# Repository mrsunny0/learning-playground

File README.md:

# Learning Playground

## Rules of Documentation

```
# [Header of README.md]
- Convention: <ROOT FOLDER NAME> - <SUBFOLDER NAME>
- Example:

## High level topic
- Example:

### Subsection of major topic
- Example:

##### Emphasized subheader
-Example:
```

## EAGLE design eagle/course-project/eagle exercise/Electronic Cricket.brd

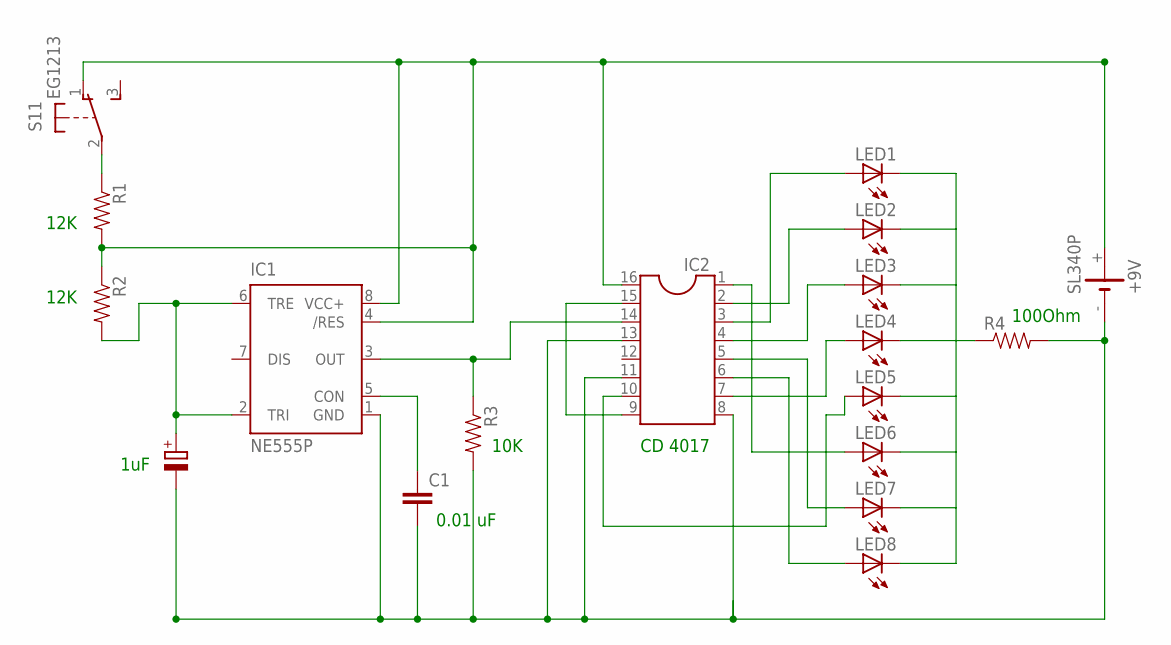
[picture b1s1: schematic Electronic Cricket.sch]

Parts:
+9V: SL340P; SL-340/P3.6V
C1: C2.5/6; C2.5-6
IC1: NE555P; DIL-08
IC2: DIL16
LED1, LED2, LED3, LED4, LED5, LED6, LED7, LED8: LEDB156; Q62902-B156
R1, R2, R3, R4: RESISTORAXIAL-0.3; AXIAL-0.3
S1: EG1213

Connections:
unnamed: IC2.3, LED1.A
unnamed: IC2.2, LED2.A
unnamed: IC2.4, LED3.A
unnamed: IC2.7, LED4.A
unnamed: IC2.10, LED5.A
unnamed: IC2.1, LED6.A
unnamed: IC2.5, LED7.A
unnamed: IC2.9, IC2.15
unnamed: +9V.-, C1.2, IC1.1 (GND), IC2.8, IC2.11, IC2.13, R3.P$2 (2), R4.P$2 (2)
unnamed: IC2.6, LED8.A
unnamed: R1.P$1 (1), S1.2
unnamed: LED1.K (C), LED2.K (C), LED3.K (C), LED4.K (C), LED5.K (C), LED6.K (C), LED7.K (C), LED8.K (C), R4.P$1 (1)
unnamed: IC1.3 (OUT), IC2.14, R3.P$1 (1)
unnamed: +9V.+, IC1.4 (/RES), IC1.8 (VCC+), IC2.16, R1.P$2 (2), R2.P$1 (1), S1.1 (O)
unnamed: IC1.2 (TRI), IC1.6 (TRE), R2.P$2 (2)
unnamed: C1.1, IC1.5 (CON)

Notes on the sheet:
12K
10K
100Ohm
1uF
0.01 uF
CD 4017

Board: 2 copper layers, 17 parts (0 on the bottom side), 16 nets, no tracks yet.

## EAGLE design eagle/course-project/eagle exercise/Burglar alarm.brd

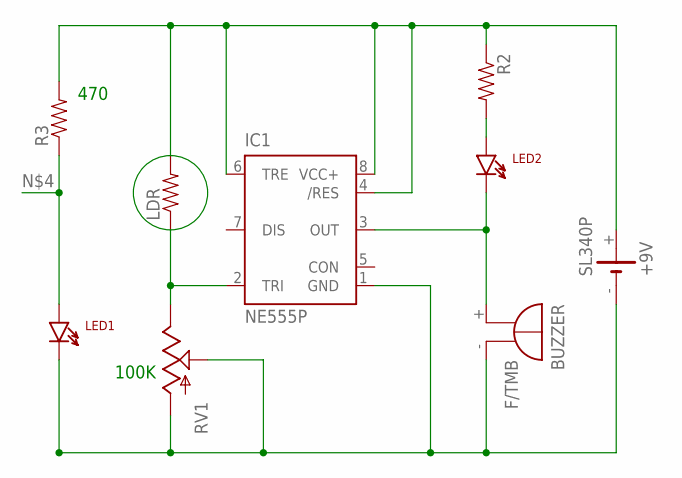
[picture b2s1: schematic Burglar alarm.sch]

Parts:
+9V: SL340P; SL-340/P3.6V
BUZZER: F/TMB
IC1: NE555P; DIL-08
LDR: RESISTORAXIAL-0.3; AXIAL-0.3
LED1, LED2: LTE-302
R2, R3: RESISTORAXIAL-0.3; AXIAL-0.3
RV1: POTTRIM; TRIM_POT

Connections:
unnamed: IC1.2 (TRI), LDR.P$1 (1), RV1.2 (E)
unnamed: BUZZER.+, IC1.3 (OUT), LED2.C
unnamed: LED2.A, R2.P$2 (2)
unnamed: LED1.A, R3.P$1 (1)
unnamed: +9V.+, IC1.4 (/RES), IC1.6 (TRE), IC1.8 (VCC+), LDR.P$2 (2), R2.P$1 (1), R3.P$2 (2)
unnamed: +9V.-, BUZZER.-, IC1.1 (GND), LED1.C, RV1.1 (S), RV1.3 (A)

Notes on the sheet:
100K
470

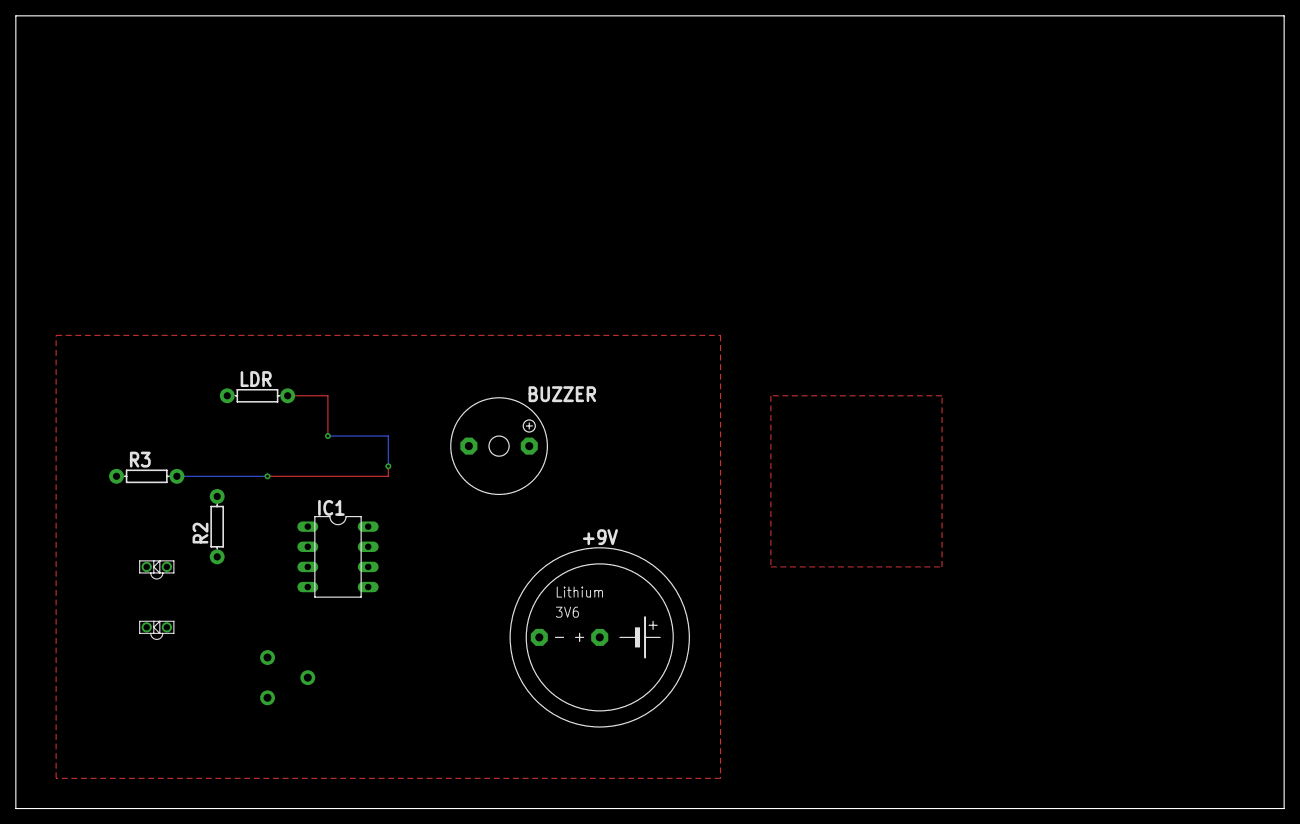
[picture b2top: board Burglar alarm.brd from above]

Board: 2 copper layers, 160.0 x 100.0 mm, 9 parts (0 on the bottom side), 6 nets.

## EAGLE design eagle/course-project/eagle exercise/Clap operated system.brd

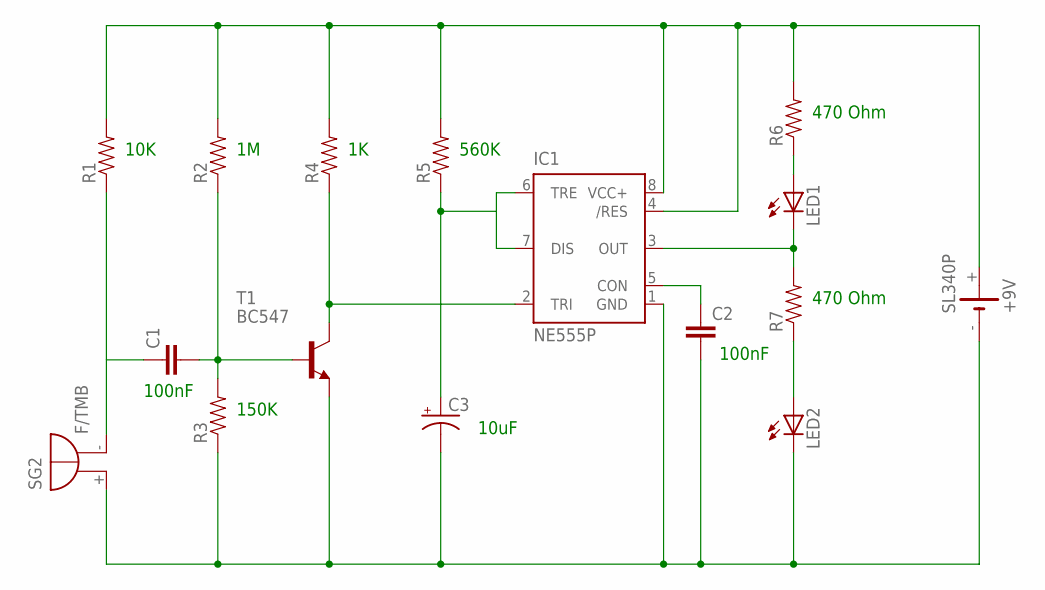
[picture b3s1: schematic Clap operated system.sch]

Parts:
+9V: SL340P; SL-340/P3.6V
C1, C2: 0.1UF-50V-20%(PTH)KIT-EZ; CAP-PTH-SMALL-KIT
C3: CAP_POLPTH1; CPOL-RADIAL-100UF-25V
IC1: NE555P; DIL-08
LED1, LED2: LED5MM
R1, R2, R3, R4, R5, R6, R7: 10KOHM1/6W5%(PTH)KIT; AXIAL-0.3-KIT
SG2: F/TMB
T1: BC547; TO92

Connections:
unnamed: C1.1, R1.P$1 (1), SG2.-
unnamed: C1.2, R2.P$1 (1), R3.P$2 (2), T1.2 (B)
unnamed: IC1.2 (TRI), R4.P$1 (1), T1.3 (C)
unnamed: C3.1 (+), IC1.6 (TRE), IC1.7 (DIS), R5.P$1 (1)
unnamed: C2.1, IC1.5 (CON)
unnamed: IC1.3 (OUT), LED1.K (C), R7.P$2 (2)
unnamed: LED2.A, R7.P$1 (1)
unnamed: +9V.+, IC1.4 (/RES), IC1.8 (VCC+), R1.P$2 (2), R2.P$2 (2), R4.P$2 (2), R5.P$2 (2), R6.P$2 (2)
unnamed: LED1.A, R6.P$1 (1)
unnamed: +9V.-, C2.2, C3.2 (-), IC1.1 (GND), LED2.K (C), R3.P$1 (1), SG2.+, T1.1 (E)

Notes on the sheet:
10K
150K
560K
470 Ohm
10uF
100nF

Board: 2 copper layers, 16 parts (0 on the bottom side), 10 nets, no tracks yet.

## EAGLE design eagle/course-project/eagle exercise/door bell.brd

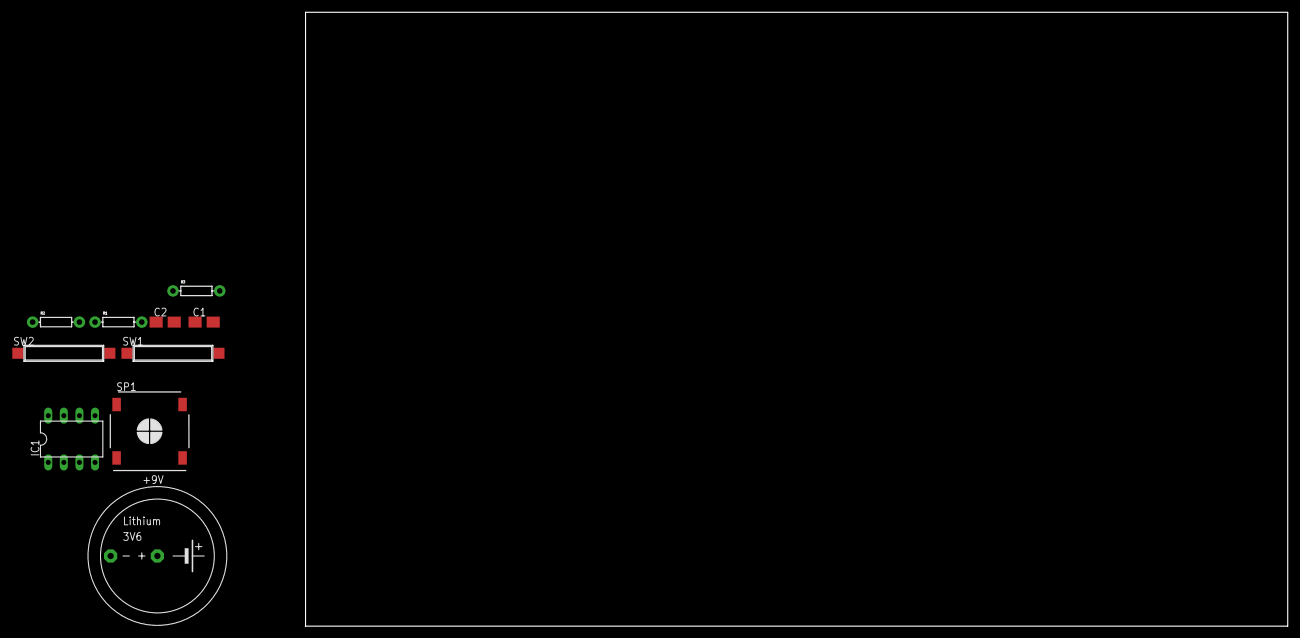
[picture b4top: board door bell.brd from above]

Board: 2 copper layers, 205.9 x 100.0 mm, 10 parts (0 on the bottom side), 8 nets, no tracks yet.

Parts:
+9V: SL340P; SL-340/P3.6V
C1, C2: A/3216-18W
IC1: NE555P; DIL-08
R1, R2, R3: AXIAL-0.3
SP1: SMS-1308MS-2-R
SW1, SW2: CT10-XXXX-A2

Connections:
unnamed: C2.+, IC1.3
unnamed: C2.-, SP1.-
unnamed: C1.+, IC1.2, IC1.6, R1.P$2
unnamed: +9V.-, C1.-, IC1.1
unnamed: R3.P$2, SW1.1
unnamed: IC1.4, IC1.8, R2.P$1, SW2.1
unnamed: IC1.7, R1.P$1, R2.P$2, R3.P$1
unnamed: +9V.+, SP1.+, SW1.2, SW2.2

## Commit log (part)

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2020-03-15 basic structure of personal playground repo
2020-03-22 unchecked website-playground course files (too large)
2020-03-22 removing css course material
2020-03-22 updating README.md
2020-03-23 changes to README.md files on README branch
2020-03-23 adding unix practice files
2020-03-31 adding and linking files in unix-playground
2020-03-31 minor fixes (redo) to git README
2020-04-01 more minor additions to README
2020-04-01 testing module import with python
2020-04-01 recommitting python playground changes
2020-04-02 Major organization, new notes for Windows README
2020-04-04 organizing and adding more content about BASH
2020-04-07 playing around with Jupyter and remote access
2020-04-07 adding gitignore to remove notebook checkpoints, etc.
2020-04-08 adding recursive call to obtain file structure with pathfinder
2020-04-09 adding lingering changes
2020-04-09 adding bluetooth dir and renaming
2020-04-14 removing course files, taking too much space
2020-04-16 renaming generators and adding files
2020-04-18 adding playground android studio files as templates
2020-04-19 working ble android connection
2020-04-21 adding files used in lesson to playground
2020-04-23 removing capitol iOS files
2020-04-26 more demo projects
2020-04-26 adding android playground files
2020-04-29 table view demo for iOS
2020-04-30 practice bash files
2020-05-01 moving scripts, adding awk script
2020-05-02 more sections and footer
2020-05-03 updating gitignore
2020-05-11 updating BLE code ios 13
2020-05-13 practicing state and data binding in swiftUI
2020-05-15 including project file in kotlin
2020-05-17 MVVM and data binding design patterns in android
2020-05-17 adding css grid work
2020-05-17 finishing touches
2020-05-19 adding more sections, background-attachment, and margin percent trick
2020-05-25 adding js to playgroud
2020-05-26 adding svg sprites from icon-moon
2020-05-26 adding content overview
2020-05-26 adding review section
2020-05-26 adding media queries for responsive flex
2020-05-27 playing with grid row and column layouts
2020-05-28 complete layout with grid names
2020-05-28 adding gallery
2020-05-29 header
2020-05-30 adding multiindex for dex limit
2020-06-07 adding d3 firebse
2020-06-07 removing firebase script, sensitive information
2020-06-07 basic wear android wear app
2020-06-07 adding phone and wear google api communication
2020-06-08 forms and form layout with list
2020-06-08 creating legend and transition updates using current val enter hack
2020-06-09 interactivity and tool tips
2020-06-09 logic in presentation, and working with date formatter
2020-06-09 x and y grid path
2020-06-09 adding ordinal scale for color scheme
2020-06-10 adding ordinal color scale
2020-06-15 removing large model file
2020-07-03 moving library to top level folder
2020-07-08 adding eagle files for practice
2020-07-20 Bump lodash in /web-dev/html-scss/playground/landing-page
    Bumps [lodash](https://github.com/lodash/lodash) from 4.17.15 to 4.17.19.
    - [Release notes](https://github.com/lodash/lodash/releases)
    - [Commits](https://github.com/lodash/lodash/compare/4.17.15...4.17.19)
2020-07-20 Bump lodash in /web-dev/html-scss/course-projects/project-02
    Bumps [lodash](https://github.com/lodash/lodash) from 4.17.15 to 4.17.19.
    - [Release notes](https://github.com/lodash/lodash/releases)
    - [Commits](https://github.com/lodash/lodash/compare/4.17.15...4.17.19)
2020-08-10 template materials for three js
2020-08-10 remaining code for cube thre js
2020-10-16 adding blinky
2020-10-21 USART and enabling interrupt on receive
2020-12-12 Bump ini from 1.3.5 to 1.3.8 in /generators/testing-ground
    Bumps [ini](https://github.com/isaacs/ini) from 1.3.5 to 1.3.8.
    - [Release notes](https://github.com/isaacs/ini/releases)
    - [Commits](https://github.com/isaacs/ini/compare/v1.3.5...v1.3.8)
2021-03-31 Bump y18n in /web-dev/html-scss/course-projects/project-01
    Bumps [y18n](https://github.com/yargs/y18n) from 3.2.1 to 3.2.2.
    - [Release notes](https://github.com/yargs/y18n/releases)
    - [Changelog](https://github.com/yargs/y18n/blob/master/CHANGELOG.md)
    - [Commits](https://github.com/yargs/y18n/commits)
2021-04-01 Bump y18n in /web-dev/html-scss/course-projects/project-03
    Bumps [y18n](https://github.com/yargs/y18n) from 3.2.1 to 3.2.2.
    - [Release notes](https://github.com/yargs/y18n/releases)
    - [Changelog](https://github.com/yargs/y18n/blob/master/CHANGELOG.md)
    - [Commits](https://github.com/yargs/y18n/commits)
2021-05-11 Bump lodash from 4.17.15 to 4.17.21 in /generators/testing-ground
    Bumps [lodash](https://github.com/lodash/lodash) from 4.17.15 to 4.17.21.
    - [Release notes](https://github.com/lodash/lodash/releases)
    - [Commits](https://github.com/lodash/lodash/compare/4.17.15...4.17.21)
2021-05-11 Bump lodash in /web-dev/html-scss/course-projects/project-03
    Bumps [lodash](https://github.com/lodash/lodash) from 4.17.15 to 4.17.21.
    - [Release notes](https://github.com/lodash/lodash/releases)
    - [Commits](https://github.com/lodash/lodash/compare/4.17.15...4.17.21)
2021-05-11 Bump hosted-git-info in /generators/generator-playground
    Bumps [hosted-git-info](https://github.com/npm/hosted-git-info) from 2.8.8 to 2.8.9.
    - [Release notes](https://github.com/npm/hosted-git-info/releases)
    - [Changelog](https://github.com/npm/hosted-git-info/blob/v2.8.9/CHANGELOG.md)
    - [Commits](https://github.com/npm/hosted-git-info/compare/v2.8.8...v2.8.9)
2021-05-11 Bump hosted-git-info in /web-dev/html-scss/course-projects/project-03
    Bumps [hosted-git-info](https://github.com/npm/hosted-git-info) from 2.8.8 to 2.8.9.
    - [Release notes](https://github.com/npm/hosted-git-info/releases)
    - [Changelog](https://github.com/npm/hosted-git-info/blob/v2.8.9/CHANGELOG.md)
    - [Commits](https://github.com/npm/hosted-git-info/compare/v2.8.8...v2.8.9)
2021-06-11 Bump glob-parent in /web-dev/html-scss/course-projects/project-01
    Bumps [glob-parent](https://github.com/gulpjs/glob-parent) from 5.1.1 to 5.1.2.
    - [Release notes](https://github.com/gulpjs/glob-parent/releases)
    - [Changelog](https://github.com/gulpjs/glob-parent/blob/main/CHANGELOG.md)
    - [Commits](https://github.com/gulpjs/glob-parent/compare/v5.1.1...v5.1.2)
    ---
    updated-dependencies:
2021-08-12 Bump path-parse in /web-dev/html-scss/playground/landing-page
    Bumps [path-parse](https://github.com/jbgutierrez/path-parse) from 1.0.6 to 1.0.7.
    - [Release notes](https://github.com/jbgutierrez/path-parse/releases)
    - [Commits](https://github.com/jbgutierrez/path-parse/commits/v1.0.7)
    ---
    updated-dependencies:
    - dependency-name: path-parse
2021-08-12 Bump path-parse from 1.0.6 to 1.0.7 in /generators/testing-ground
    Bumps [path-parse](https://github.com/jbgutierrez/path-parse) from 1.0.6 to 1.0.7.
    - [Release notes](https://github.com/jbgutierrez/path-parse/releases)
    - [Commits](https://github.com/jbgutierrez/path-parse/commits/v1.0.7)
    ---
    updated-dependencies:
    - dependency-name: path-parse
2022-01-15 Bump shelljs from 0.8.3 to 0.8.5 in /generators/generator-playground
    Bumps [shelljs](https://github.com/shelljs/shelljs) from 0.8.3 to 0.8.5.
    - [Release notes](https://github.com/shelljs/shelljs/releases)
    - [Changelog](https://github.com/shelljs/shelljs/blob/master/CHANGELOG.md)
    - [Commits](https://github.com/shelljs/shelljs/compare/v0.8.3...v0.8.5)
    ---
    updated-dependencies:
2022-02-10 Bump node-sass in /web-dev/html-scss/course-projects/project-02
    Bumps [node-sass](https://github.com/sass/node-sass) from 4.14.1 to 7.0.0.
    - [Release notes](https://github.com/sass/node-sass/releases)
    - [Changelog](https://github.com/sass/node-sass/blob/master/CHANGELOG.md)
    - [Commits](https://github.com/sass/node-sass/compare/v4.14.1...v7.0.0)
    ---
    updated-dependencies:
2022-02-13 Bump ajv in /web-dev/html-scss/course-projects/project-01
    Bumps [ajv](https://github.com/ajv-validator/ajv) from 6.12.2 to 6.12.6.
    - [Release notes](https://github.com/ajv-validator/ajv/releases)
    - [Commits](https://github.com/ajv-validator/ajv/compare/v6.12.2...v6.12.6)
    ---
    updated-dependencies:
    - dependency-name: ajv
2022-02-13 Bump ajv in /web-dev/html-scss/course-projects/project-03
    Bumps [ajv](https://github.com/ajv-validator/ajv) from 6.12.2 to 6.12.6.
    - [Release notes](https://github.com/ajv-validator/ajv/releases)
    - [Commits](https://github.com/ajv-validator/ajv/compare/v6.12.2...v6.12.6)
    ---
    updated-dependencies:
    - dependency-name: ajv
2022-03-26 Bump minimist in /web-dev/html-scss/playground/landing-page
    Bumps [minimist](https://github.com/substack/minimist) from 1.2.5 to 1.2.6.
    - [Release notes](https://github.com/substack/minimist/releases)
    - [Commits](https://github.com/substack/minimist/compare/1.2.5...1.2.6)
    ---
    updated-dependencies:
    - dependency-name: minimist
2022-03-26 Bump minimist in /web-dev/html-scss/course-projects/project-03
    Bumps [minimist](https://github.com/substack/minimist) from 1.2.5 to 1.2.6.
    - [Release notes](https://github.com/substack/minimist/releases)
    - [Commits](https://github.com/substack/minimist/compare/1.2.5...1.2.6)
    ---
    updated-dependencies:
    - dependency-name: minimist
2022-05-19 Bump nokogiri from 1.10.8 to 1.13.6 in /generators/testing-ground
    Bumps [nokogiri](https://github.com/sparklemotion/nokogiri) from 1.10.8 to 1.13.6.
    - [Release notes](https://github.com/sparklemotion/nokogiri/releases)
    - [Changelog](https://github.com/sparklemotion/nokogiri/blob/main/CHANGELOG.md)
    - [Commits](https://github.com/sparklemotion/nokogiri/compare/v1.10.8...v1.13.6)
    ---
    updated-dependencies:
2022-06-23 Bump shell-quote in /web-dev/html-scss/course-projects/project-03
    Bumps [shell-quote](https://github.com/substack/node-shell-quote) from 1.7.2 to 1.7.3.
    - [Release notes](https://github.com/substack/node-shell-quote/releases)
    - [Changelog](https://github.com/substack/node-shell-quote/blob/master/CHANGELOG.md)
    - [Commits](https://github.com/substack/node-shell-quote/compare/v1.7.2...1.7.3)
    ---
    updated-dependencies:
2022-07-22 Bump tzinfo from 1.2.7 to 1.2.10 in /generators/testing-ground
    Bumps [tzinfo](https://github.com/tzinfo/tzinfo) from 1.2.7 to 1.2.10.
    - [Release notes](https://github.com/tzinfo/tzinfo/releases)
    - [Changelog](https://github.com/tzinfo/tzinfo/blob/master/CHANGES.md)
    - [Commits](https://github.com/tzinfo/tzinfo/compare/v1.2.7...v1.2.10)
    ---
    updated-dependencies:
2022-11-23 Bump engine.io and browser-sync in /generators/testing-ground
    Bumps [engine.io](https://github.com/socketio/engine.io) to 6.2.1 and updates ancestor dependency [browser-sync](https://github.com/BrowserSync/browser-sync). These dependencies need to be updated to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
    Updates `engine.io` from 3.2.1 to 6.2.1
    - [Release notes](https://github.com/socketio/engine.io/releases)
    - [Changelog](https://github.com/socketio/engine.io/blob/main/CHANGELOG.md)
    - [Commits](https://github.com/socketio/engine.io/compare/3.2.1...6.2.1)
    Updates `browser-sync` from 2.26.7 to 2.27.10
2022-12-06 Bump decode-uri-component
    Bumps [decode-uri-component](https://github.com/SamVerschueren/decode-uri-component) from 0.2.0 to 0.2.2.
    - [Release notes](https://github.com/SamVerschueren/decode-uri-component/releases)
    - [Commits](https://github.com/SamVerschueren/decode-uri-component/compare/v0.2.0...v0.2.2)
    ---
    updated-dependencies:
    - dependency-name: decode-uri-component

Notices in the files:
parts and their libraries:
SparkFun-AnalogIC: Licensing: CC v3.0 Share-Alike You are welcome to use this library for commercial purposes.
SparkFun-Retired: Licensing: Creative Commons ShareAlike 4.0 International - https://creativecommons.org/licenses/by-sa/4.0
